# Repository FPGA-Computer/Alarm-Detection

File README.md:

"Alarm detection for hearing impaired"

This is the repository for this project.

Project page:
https://hackaday.io/project/12703

Schematic tool: Eagle CAD 6.5.0
3D modelling: Sketchup 14.1 2014

Licensing:
Schematic: Creative Commons 4.0 Attribution-ShareAlike 4.0 International
PCB & Layout: Creative Commons 4.0 Attribution-NonCommercial
3D modelling: Creative Commons 4.0 Attribution-ShareAlike 4.0 International

Creative Commons 4.0 Attribution-NonCommercial:
See http://creativecommons.org/licenses/by-nc/4.0/

Creative Commons 4.0 Attribution-ShareAlike 4.0 International
See http://creativecommons.org/licenses/by-sa/4.0/

Firmware license: GPL 3.0

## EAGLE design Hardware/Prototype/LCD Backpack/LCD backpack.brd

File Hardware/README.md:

"Alarm detection for hearing impaired"

Since the common block is useful for a few of my projects, 
I have splitted off the hardware design into smaller modular 
block for initial prototyping.

LCD Backpack: STM32F030 based PCB for mounting onto the back 
of a "Nokia" LCD.  It has anti-alias RC filter for ADC and an 
optional 3.3V boost mode power supply for running off two
Alkaline/NiMH batteries.

The firmware is based on the VU/Spectrum analyzer of the 
"Automatic-Audio-Switch".  I have increase the FFT resolution 
to about 37.5Hz and a bandwidth of 5kHz.

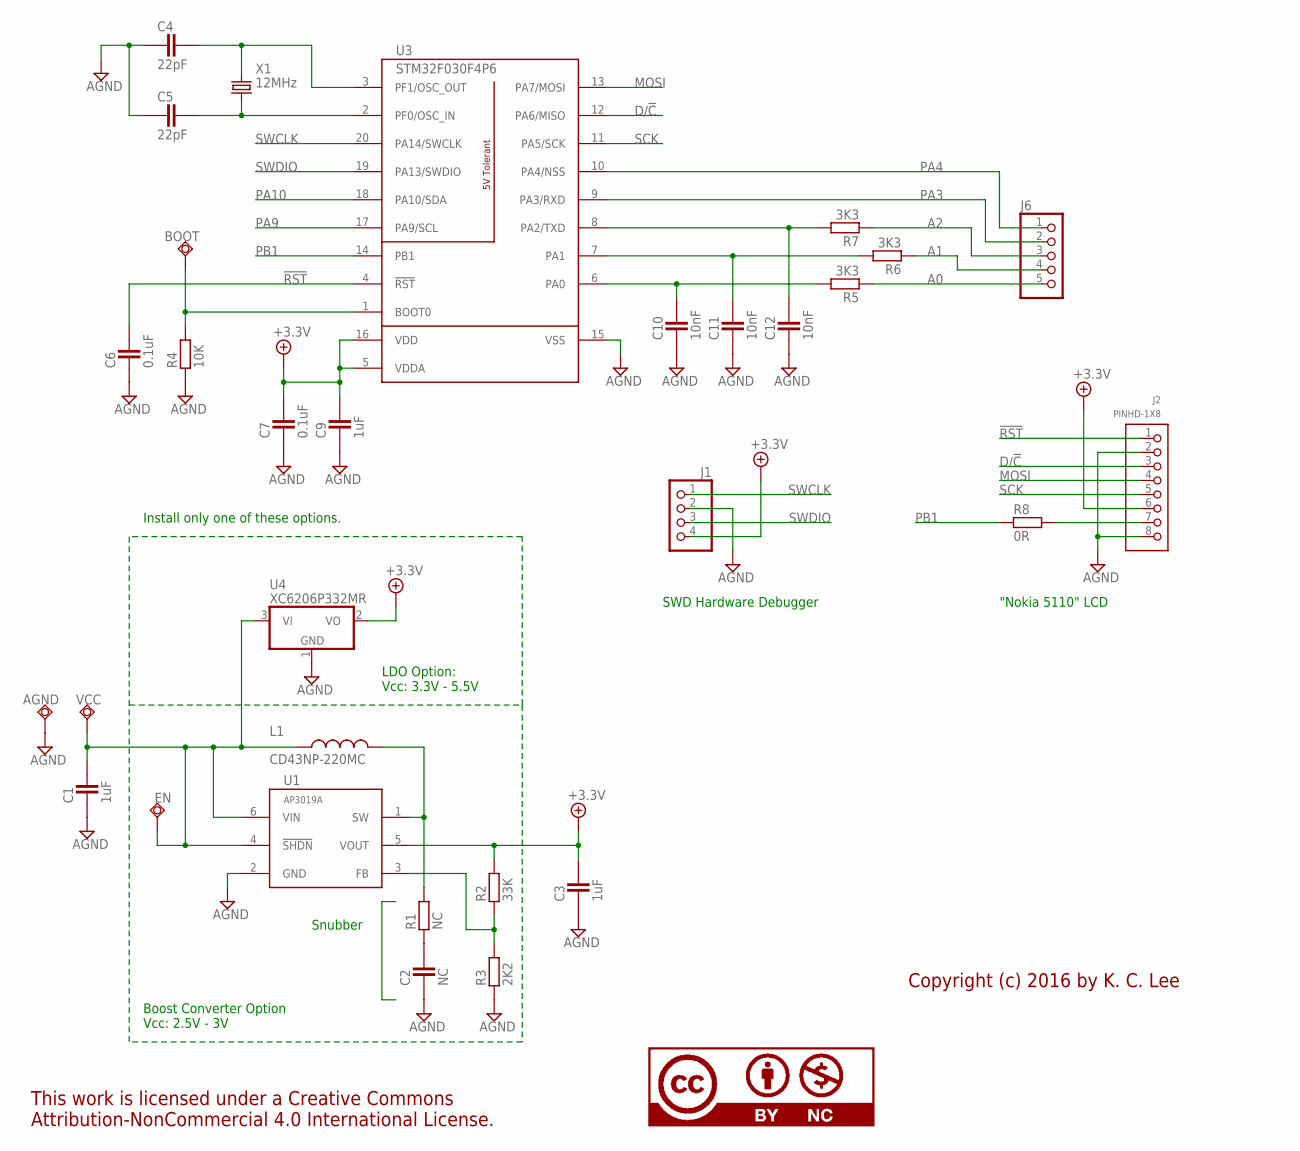
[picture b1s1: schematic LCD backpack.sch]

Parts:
AGND: TPSQTP10SQ; TP10SQ; PARTNO TESTPAD
BOOT: TPSQTP10SQ; TP10SQ; PARTNO TESTPAD
C1, C3, C9: 1uF; CAPC1608X92N; PARTNO STOCK: 1UF/10V 20% TDK
C2: NC; CAPC1608X92N; PARTNO *
C4, C5: 22pF; CAPC1608X92N; PARTNO *
C6, C7: 0.1uF; CAPC1608X92N; PARTNO *
C10, C11, C12: 10nF; CAPC1608X92N; PARTNO *
EN: TPSQTP06SQ; TP06SQ; PARTNO TESTPAD
J1: PINHD-1X4_2.54; 1X04; PARTNO 1x04 header 2.54mm
J2: PINHD-1X8; 1X08; PARTNO 1x08 header 2.54mm
J6: PINHD-1X5_2.00; 1X05M; PARTNO 1X5 header 2MM
L1: CD43NP-220MC; CD43; PARTNO DK: 587-1626-1-ND
LICENSE1: CC-BY-NCNONE; CC-NONE; PARTNO *
R1: NC; RESC1608X55N; PARTNO *
R2: 33K; RESC1608X55N; PARTNO *
R3: 2K2; RESC1608X55N; PARTNO *
R4: 10K; RESC1608X55N; PARTNO *
R5, R6, R7: 3K3; RESC1608X55N; PARTNO *
R8: 0R; RESC1608X55N; PARTNO *
U1: AP3019A; SOT26; PARTNO AP3019AKTR-G1
U3: STM32F030F4P6; TSSOP20; PARTNO *
U4: XC6206P332MR; SOT95P280X135-3N; PARTNO *
VCC: TPSQTP10SQ; TP10SQ; PARTNO TESTPAD
X1: 12MHz; HC49U-V; PARTNO *

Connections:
!RST: C6.2, J2.1, U3.4 (!RST)
+3.3V: C3.2, C7.2, C9.2, J1.4, J2.6, R2.2, U1.5 (VOUT), U3.5 (VDDA), U3.16 (VDD), U4.2 (VO)
A0: J6.5, R5.1
A1: J6.4, R6.1
A2: J6.3, R7.1
AGND: AGND.TP, C1.1, C2.1, C3.1, C4.1, C5.1, C6.1, C7.1, C9.1, C10.1, C11.1, C12.1, J1.2, J2.2, J2.8, R3.1, R4.1, U1.2 (GND), U3.15 (VSS), U4.1 (GND)
BUTTON: C12.2, R7.2, U3.8 (PA2/TXD)
D/!C: J2.3, U3.12 (PA6/MISO)
MOSI: J2.4, U3.13 (PA7/MOSI)
unnamed: C2.2, R1.1
unnamed: J2.7, R8.2
unnamed: L1.1, R1.2, U1.1 (SW)
unnamed: R2.1, R3.2, U1.3 (FB)
unnamed: BOOT.TP, R4.2, U3.1 (BOOT0)
unnamed: C10.2, R5.2, U3.6 (PA0)
unnamed: C11.2, R6.2, U3.7 (PA1)
unnamed: C5.2, U3.2 (PF0/OSC_IN), X1.1
unnamed: C4.2, U3.3 (PF1/OSC_OUT), X1.2
PA3: J6.2, U3.9 (PA3/RXD)
PA4: J6.1, U3.10 (PA4/NSS)
PA9: U3.17 (PA9/SCL)
PA10: U3.18 (PA10/SDA)
PB1: R8.1, U3.14 (PB1)
SCK: J2.5, U3.11 (PA5/SCK)
SWCLK: J1.1, U3.20 (PA14/SWCLK)
SWDIO: J1.3, U3.19 (PA13/SWDIO)
VCC: C1.2, EN.TP, L1.2, U1.4 (!SHDN), U1.6 (VIN), U4.3 (VI), VCC.TP

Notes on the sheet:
SWD Hardware Debugger
Copyright (c) 2016 by K. C. Lee
Snubber
Boost Converter Option Vcc: 2.5V - 3V
LDO Option: Vcc: 3.3V - 5.5V
Install only one of these options.
"Nokia 5110" LCD

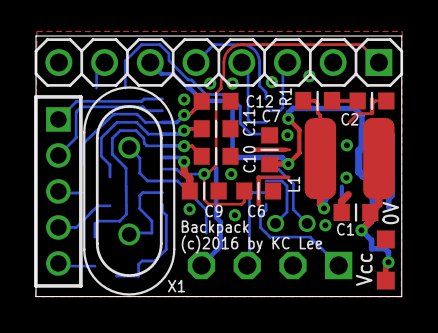
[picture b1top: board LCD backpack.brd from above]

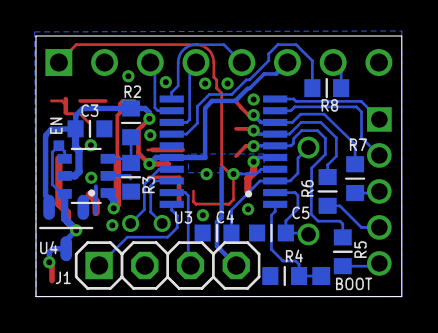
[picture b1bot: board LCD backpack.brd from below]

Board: 2 copper layers, 20.3 x 14.5 mm, 32 parts (16 on the bottom side), 25 nets.

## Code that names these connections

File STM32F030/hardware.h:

/*
 * hardware.h
 *
 * Created: March-14-16, 4:52:17 PM
 *  Author: K. C. Lee
 * Copyright (c) 2016 by K. C. Lee 
 
 	This program is free software: you can redistribute it and/or modify
	it under the terms of the GNU General Public License as published by
	the Free Software Foundation, either version 3 of the License, or
	(at your option) any later version.

	This program is distributed in the hope that it will be useful,
	but WITHOUT ANY WARRANTY; without even the implied warranty of
	MERCHANTABILITY or FITNESS FOR A PARTICULAR PURPOSE.  See the
	GNU General Public License for more details.

	You should have received a copy of the GNU General Public License
	along with this program.

	If not, see http://www.gnu.org/licenses/gpl-3.0.en.html
 */ 

#ifndef _HARDWARE_H_
#define _HARDWARE_H_

#include "main.h"
#include "gpio.h"

#define MIN(X,Y)							(((X)<=(Y))?(X):(Y))

#define CPU_CLOCK							8000000UL
#define UART_BAUD							115200

#define HSE_CLOCK							8000000UL

// SCK = Clk/2 = 4MHz
#define SPI_BR								0

#define LCD_DMA_IRQ_PRIORITY	3

// Enable Debug shell 
//#define DBG_SHELL
#undef DBG_SHELL

//#define ADC_RES_8
#define ADC_RES_12

#define BACKLIGHT							PB1
#define LCD_DC								PA6
#define ADC_BATT_IN						PA1
#define ADC_MIC_IN						PA0

#define ADC_SRC_GROUP					(1<<ADC_MIC_IN)
#define ADC_BATTERY						(1<<ADC_BATT_IN)

#define ADC_AVERAGES					(VOLUME_AVERAGE_PERIOD*ADC_SAMPLE_RATE/ADC_BLOCK_SIZE/1000)
#define ADC_BATT_SCALE_MULT		2505UL
#define ADC_BATT_SCALE_DIV		2509UL

// Max # of audio source
#define ADC_MAX_SRC						1
// L/R channels
#define ADC_CH_PER_SRC				1
#define ADC_MAX_AUD_CH				1
// Max # of channels per conversion
#define ADC_MAX_CH						ADC_MAX_AUD_CH

#include "main.h"
#include "nokia5110.h"
#include "adc.h"
#include "audio.h"
//#include "fifo.h"

void Hardware_Init(void);

enum ADC_Chs
{
	Audio_R1, Audio_L1, Audio_R0, Audio_L0, Buttons
};

#define GPIOA_MODER (PIN_ALT(PA14)|PIN_ALT(PA13)|				/* SWCLK, SWDIO */	\
										 PIN_OUTPUT(PA10)|PIN_OUTPUT(PA9)|	/* CTRL1, CTRL0	*/	\
										 PIN_ALT(PA7)|PIN_OUTPUT(PA6)|			/* MOSI, D/C 		*/	\
										 PIN_ALT(PA5)|PIN_OUTPUT(PA4)|			/* SCK, ???			*/	\
										 PIN_OUTPUT(PA3)|PIN_OUTPUT(PA2)|		/* ???, ???			*/	\
		                 PIN_ANALOG(PA1)|PIN_ANALOG(PA0))		/* ???, Analog in	*/
										 
#define CTRL1				PA3
#define CTRL0				PA2

#define GPIOA_AFR1	0

// low priority
#define SPI_DMA_PRIORITY    0

void SPI_Block_Write(const uint8_t *ptr, uint16_t size);
void SPI_Block_Fill(uint8_t Fill, uint16_t size);

void SPI_ByteWrite(uint8_t byte);

void DMA_memmove(void *Dst, void *Src, uint16_t Size);
void DMA_memset(void *Dst, uint8_t fill, uint16_t Size);
#endif

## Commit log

2016-08-18 Lost in space - initial commit
2016-09-30 Visualization
2016-10-02 DMA mem func & reorg
2016-10-08 Frequency readout

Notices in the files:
parts and their libraries:
Misc logo: This work is licensed under a Creative Commons
Attribution-NonCommercial 4.0 International License.
